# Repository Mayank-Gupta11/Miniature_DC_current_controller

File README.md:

# Miniature_DC_current_controller
This is a DC current controller which can control currents in the range of 0-3A. These are the files and the report, for the course Electronic Design Lab

User manual:-  The document contains detailed info specifications, terminologies definitions, and instructions to use for the user along with additional instructions the user should take care of.

Design_documentation:- The document contains an overview of the project with the circuit as well as a block diagram. It also provides an overview of the CC-CV modes and control mechanisms.

PCB:- The directory contains .sch files which include schematic files and .pcb has placement and routing of components in the circuit.

CAD:- The directory contains all files for the final CAD assembly model of the project. It has mounting holes for wall attachment; each surface has groves for fitting a removable back panel structure.

Microcontroller_code:- The directory contains all code files of STM32 uC. The code contains a control algorithm for current, CC-CV mode transition, code for rotary encoder, hall-based current sensor to sense the current and setting reference voltage corresponding to current interfaces with DAC.

Test results:- The document includes test methodologies for the basic circuit, microcontroller integration, CC-CV switching and UART interfacing and the results of each methodology.

Frontend:- This contains python code for the web based GUI for UART control.

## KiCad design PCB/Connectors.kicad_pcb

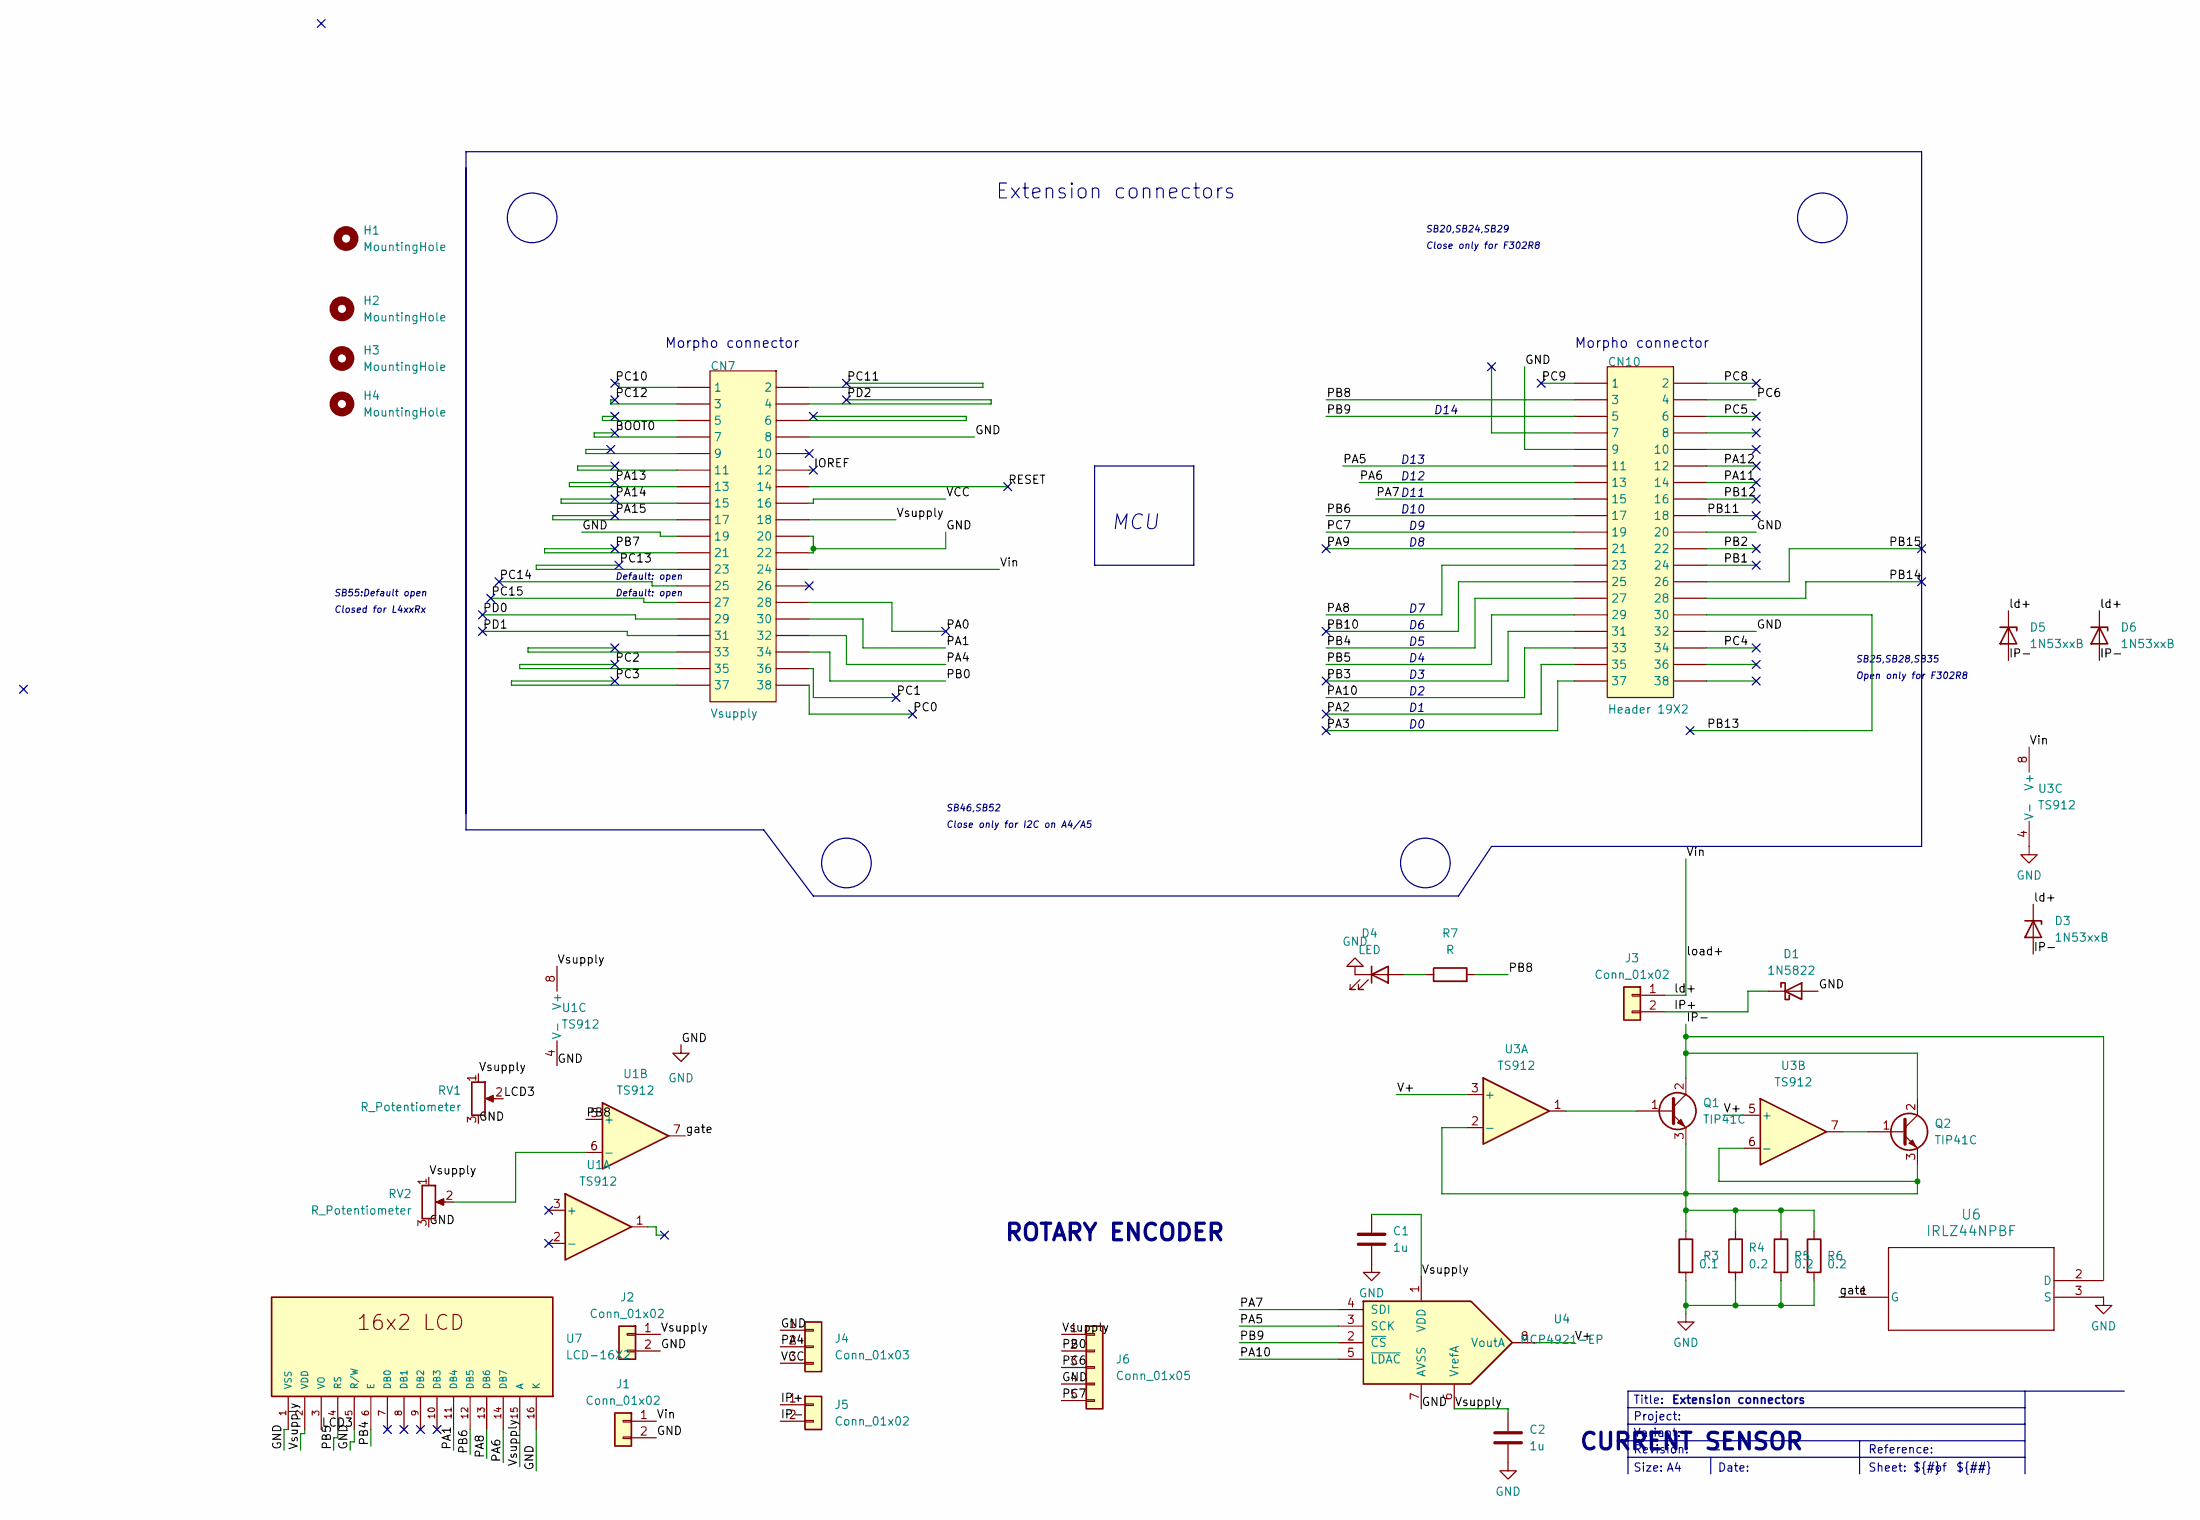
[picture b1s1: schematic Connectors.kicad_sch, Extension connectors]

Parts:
C1, C2: 1u; C_1206_3216Metric
CN7: Vsupply; PinSocket_2x19_P2.54mm_Vertical
CN10: Header 19X2; PinSocket_2x19_P2.54mm_Vertical
D1: 1N5822; D_DO-201AD_P15.24mm_Horizontal
D3, D5, D6: 1N53xxB; D_DO-201_P15.24mm_Horizontal
D4: LED; LED_1206_3216Metric
H1, H2, H3, H4: MountingHole; MountingHole_2.5mm
J1, J3: Conn_01x02; PinSocket_1x02_P2.54mm_Vertical
J2, J5: Conn_01x02; PinHeader_1x02_P2.54mm_Vertical
J4: Conn_01x03; PinSocket_1x03_P2.54mm_Vertical
J6: Conn_01x05; PinHeader_1x05_P2.54mm_Vertical
Q1, Q2: TIP41C; TO-220-3_Vertical
R3: 0.1; R_Axial_Power_L25.0mm_W9.0mm_P30.48mm
R4, R5, R6: 0.2; R_Axial_DIN0614_L14.3mm_D5.7mm_P25.40mm_Horizontal
R7: R; R_Axial_DIN0204_L3.6mm_D1.6mm_P7.62mm_Horizontal
RV1, RV2: R_Potentiometer; Potentiometer_Bourns_3386P_Vertical
U1, U3: TS912; TLV_bb
U4: MCP4921-EP; DIP-8_W7.62mm
U6: IRLZ44NPBF; PG-TO220-3_INF
U7: LCD-16X2; MODULE_LCD-16X2; PARTREV N/A

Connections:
/BOOT0: CN7.7
/IOREF: CN7.12
/IP+: D1.1 (K), J3.2, J5.1
/IP-: D3.2 (A), D5.2 (A), D6.2 (A), J5.2, Q1.2 (C), Q2.2 (C), U6.2 (D)
/LCD3: RV1.2, U7.3 (VO)
/PA0: CN7.28
/PA1: CN7.30, U7.11 (DB4)
/PA2: CN10.35
/PA3: CN10.37
/PA4: CN7.32, J4.2
/PA5: CN10.11, U4.3 (SCK)
/PA6: CN10.13, U7.14 (DB7)
/PA7: CN10.15, U4.4 (SDI)
/PA8: CN10.23, U7.13 (DB6)
/PA9: CN10.21
/PA10: CN10.33, U4.5 (~LDAC)
/PA11: CN10.14
/PA12: CN10.12
/PA13: CN7.13
/PA14: CN7.15
/PA15: CN7.17
/PB0: CN7.34, J6.2
/PB1: CN10.24
/PB2: CN10.22
/PB3: CN10.31
/PB4: CN10.27, U7.6 (E)
/PB5: CN10.29, U7.4 (RS)
/PB6: CN10.17, U7.12 (DB5)
/PB7: CN7.21
/PB8: CN10.3, R7.2, U1.5 (+)
/PB9: CN10.5, U4.2 (~CS)
/PB10: CN10.25
/PB11: CN10.18
/PB12: CN10.16
/PB13: CN10.30
/PB14: CN10.28
/PB15: CN10.26
/PC0: CN7.38
/PC1: CN7.36
/PC2: CN7.35
/PC3: CN7.37
/PC4: CN10.34
/PC5: CN10.6
/PC6: CN10.4, J6.3
/PC7: CN10.19, J6.5
/PC8: CN10.2
/PC9: CN10.1
/PC10: CN7.1
/PC11: CN7.2
/PC12: CN7.3
/PC13: CN7.23
/PC14: CN7.25
/PC15: CN7.27
/PD0: CN7.29
/PD1: CN7.31
/PD2: CN7.4
/RESET: CN7.14
/V+: U3.3 (+), U3.5 (+), U4.8 (VoutA)
/VCC: CN7.16, J4.3
/Vin: CN7.24, D3.1 (K), D5.1 (K), D6.1 (K), J1.1, J3.1, U3.8 (V+)
/Vsupply: C1.1, C2.1, CN7.18, J2.1, J6.1, RV1.1, RV2.1, U1.8 (V+), U4.1 (VDD), U4.6 (VrefA), U7.2 (VDD), U7.15 (A)
/gate: U1.7, U6.1 (G)
GND: C1.2, C2.2, CN7.8, CN7.19, CN7.20, CN7.22, CN10.9, CN10.20, CN10.32, D1.2 (A), D4.1 (K), J1.2, J2.2, J4.1, J6.4, R3.2, R4.2, R5.2, R6.2, RV1.3, RV2.3, U1.4 (V-), U3.4 (V-), U4.7 (AVSS), U6.3 (S), U7.1 (VSS), U7.5 (R/W), U7.16 (K)
unnamed: D4.2 (A), R7.1
unnamed: Q1.1 (B), U3.1
unnamed: Q1.3 (E), Q2.3 (E), R3.1, R4.1, R5.1, R6.1, U3.2 (-), U3.6 (-)
unnamed: Q2.1 (B), U3.7
unnamed: RV2.2, U1.6 (-)

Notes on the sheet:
SB20,SB24,SB29
Size:
${#}
Close only for I2C on A4/A5
Revision:
Morpho connector
CURRENT SENSOR
Close only for F302R8
D13
${##}
ROTARY ENCODER
D11
Extension connectors
Title:
Sheet:
Reference:
D10
Project:
Closed for L4xxRx
Default: open
MCU
Open only for F302R8
Variant:
Date:
SB55:Default open
${TITLE}
D14
SB46,SB52
D12
SB25,SB28,SB35

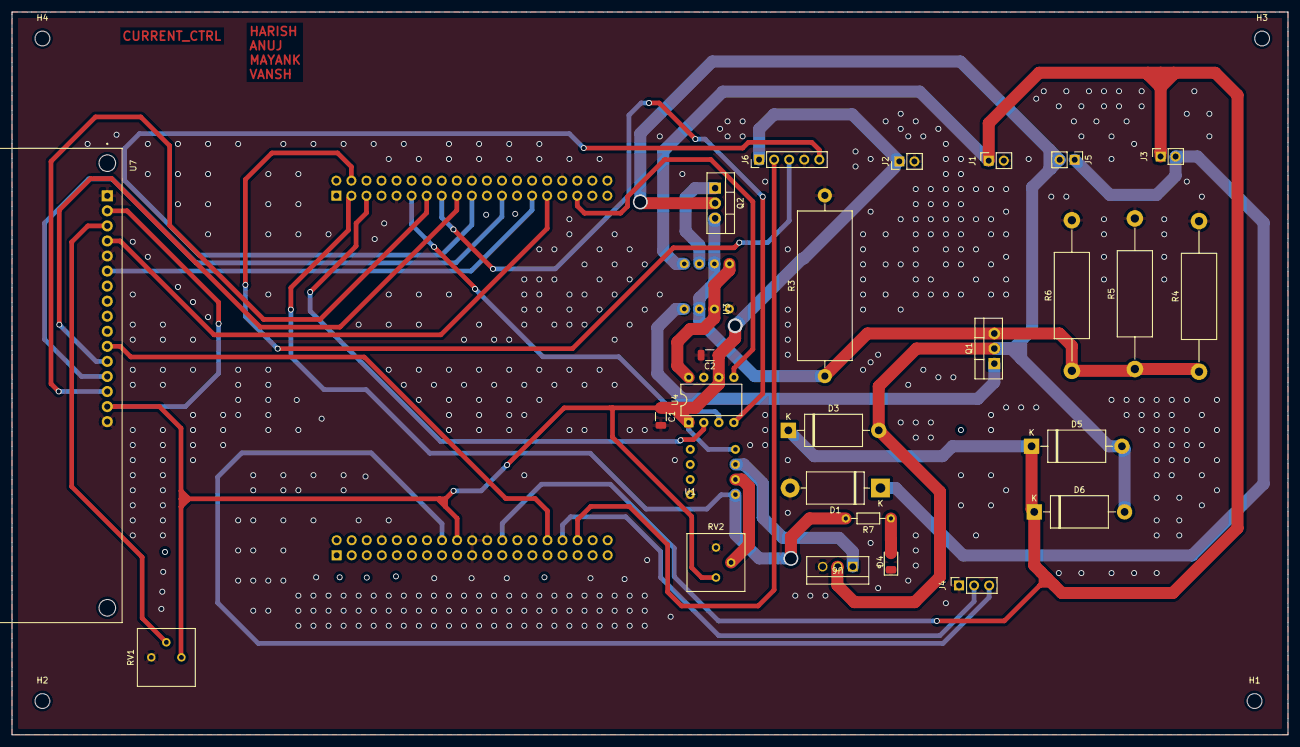
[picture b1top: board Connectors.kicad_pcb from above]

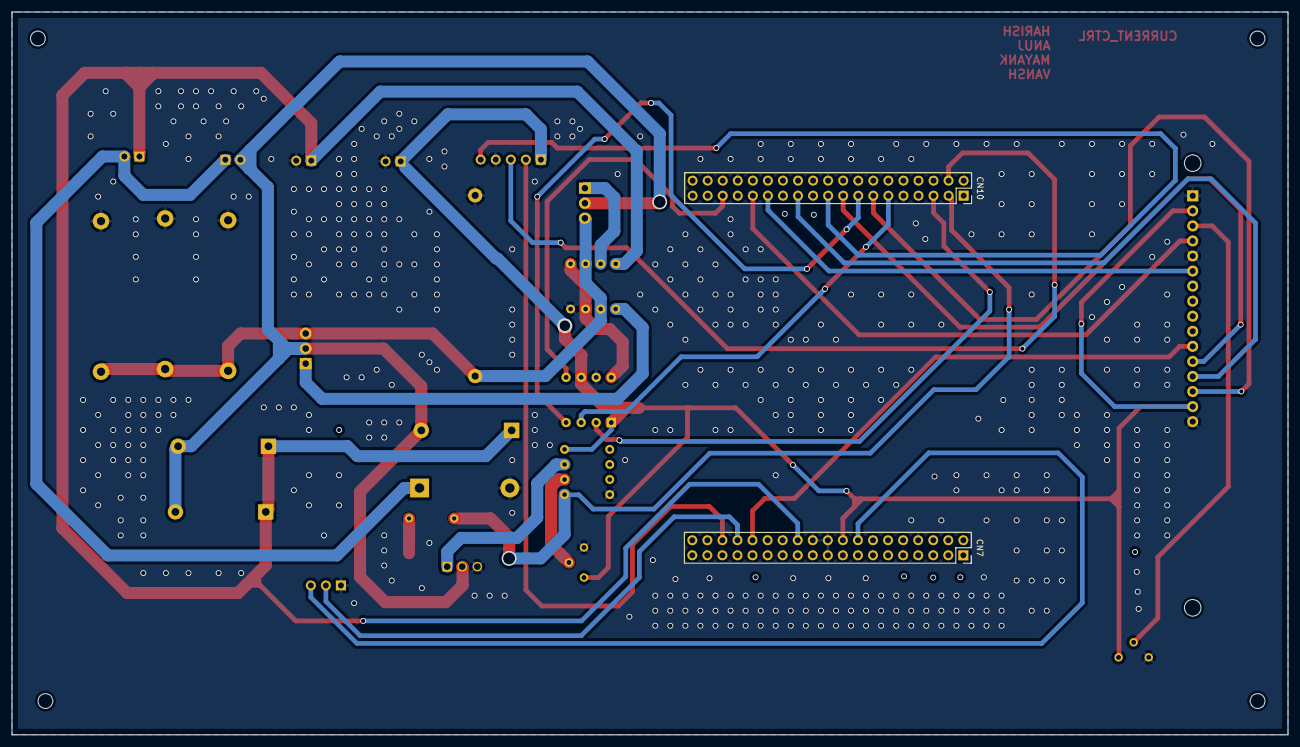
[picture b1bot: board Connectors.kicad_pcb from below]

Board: 2 copper layers, 215.2 x 121.9 mm, 33 parts (2 on the bottom side), 29 nets.

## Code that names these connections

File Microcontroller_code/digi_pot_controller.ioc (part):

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Mcu.Name=STM32F103R(8-B)Tx
Mcu.Package=LQFP64
Mcu.UserName=STM32F103RBTx
PA0-WKUP.Signal=ADCx_IN0
PA1.Signal=GPIO_Output
PA10.Signal=GPIO_Output
PA2.Mode=Asynchronous
PA2.Signal=USART2_TX
PA3.Mode=Asynchronous
PA3.Signal=USART2_RX
PA4.Signal=ADCx_IN4
PA5.Mode=TX_Only_Simplex_Unidirect_Master
PA5.Signal=SPI1_SCK
PA6.Signal=GPIO_Output
PA7.Mode=TX_Only_Simplex_Unidirect_Master
PA7.Signal=SPI1_MOSI
PA8.Signal=GPIO_Output
PB0.GPIOParameters=GPIO_PuPd
PB0.GPIO_PuPd=GPIO_PULLDOWN
PB0.Signal=GPIO_Input
PB4.Signal=GPIO_Output
PB5.Signal=GPIO_Output
PB6.Signal=GPIO_Output
PB8.GPIOParameters=GPIO_PuPd
PB8.GPIO_PuPd=GPIO_NOPULL
PB8.Signal=GPIO_Output
PB9.Signal=GPIO_Output
PC6.GPIOParameters=GPIO_PuPd
PC6.GPIO_PuPd=GPIO_PULLUP
PC6.Signal=S_TIM3_CH1
PC7.GPIOParameters=GPIO_PuPd
PC7.GPIO_PuPd=GPIO_PULLUP
PC7.Signal=S_TIM3_CH2
RCC.SYSCLKFreq_VALUE=36000000
RCC.SYSCLKSource=RCC_SYSCLKSOURCE_PLLCLK
board=NUCLEO-F103RB
boardIOC=true

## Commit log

2024-12-01 Fixed formatting issue
